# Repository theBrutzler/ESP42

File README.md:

# ESP42
ESP42 -> ESP01

it has 4MB Flash and 2MB of Ram

I created a board, that could fit an ESP32 on a ESP01 standard pinout.

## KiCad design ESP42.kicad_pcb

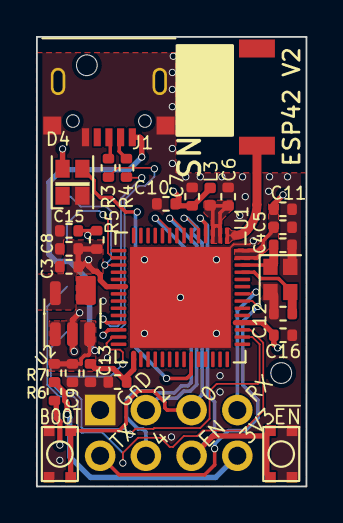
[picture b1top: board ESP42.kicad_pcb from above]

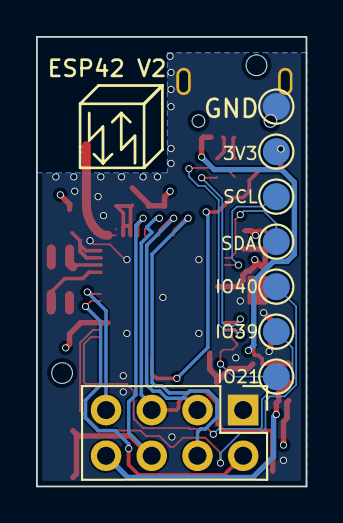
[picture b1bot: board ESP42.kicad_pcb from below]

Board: 4 copper layers, 15.0 x 25.0 mm, 37 parts (9 on the bottom side), 25 nets.

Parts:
3V3: TestPoint; TestPoint_Pad_D1.5mm
AE1: Antenna_Shield; RFANT5220110A2T
C3, C9: 10µ; R_0402_1005Metric
C4, C12: 15p; R_0402_1005Metric
C5, C6, C7, C8, C14, C16: 100n; R_0402_1005Metric
C10, C11, C13, C15: 1µ; R_0402_1005Metric
D4: WS2812B_Geaendertes_Symbol; LED_Cree-PLCC4_2x2mm_CCW
GND: TestPoint; TestPoint_Pad_D1.5mm
IO21, IO39, IO40: TestPoint; TestPoint_Pad_D1.5mm
J1: USB_B_Micro; 10118194
J2: Conn_02x04_Odd_Even; PinHeader_2x04_P2.54mm_Vertical
L3: 2n2; L_0402_1005Metric
R3, R4: 22; R_0402_1005Metric
R5: 5K1; R_0402_1005Metric
R6, R7: 0; R_0402_1005Metric
SCL: TestPoint; TestPoint_Pad_D1.5mm
SDA: TestPoint; TestPoint_Pad_D1.5mm
SM3: SYM_Arrow45_Tiny; Symbol_kurzschlussblog
SW1, SW2: SW_Push; microswitch
U1: ESP32-S3; QFN-56-1EP_7x7mm_P0.4mm_EP5.6x5.6mm
U2: LN1134A332MR; TSOT-23-5
Y1: 40MHz; Crystal_SMD_2016-4Pin_2.0x1.6mm

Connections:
+3V3: 3V3.1, C3.1, C5.2, C7.2, C8.2, C10.2, C11.2, C16.2, D4.4 (VDD), L3.1, R5.1, R6.2, U1.20 (VDD3P3_RTC), U1.46 (VDD3P3_CPU), U1.55 (VDDA), U1.56 (VDDA), U2.5 (VOUT)
/D+: R3.1, U1.26 (GPIO20/USB_D+/ADC2_CH9)
/D-: R4.1, U1.25 (GPIO19/USB_D-/ADC2_CH8)
/EN: C15.1, J2.6, R5.2, SW1.2, U1.4 (CHIP_PU/RESET)
/IO0: J2.5, SW2.2, U1.5 (GPIO0/BOOT)
/IO2: J2.3, U1.7 (GPIO2/ADC1_CH1)
/IO4: J2.4, U1.9 (GPIO4/ADC1_CH3)
/IO47: D4.3 (DIN), U1.37 (SPICLK_P/GPIO47)
/RX: J2.7, U1.50 (U0RXD/PROG/GPIO44)
/SCL: SCL.1, U1.17 (GPIO12/ADC2_CH1)
/SDA: SDA.1, U1.16 (GPIO11/ADC2_CH0)
/TX: J2.2, U1.49 (U0TXD/PROG/GPIO43)
/VIN: C9.1, J1.1 (VBUS), R7.1, U2.1 (VIN), U2.3 (EN)
GND: C3.2, C4.2, C5.1, C6.1, C7.1, C8.1, C9.2, C10.1, C11.1, C12.2, C13.1, C14.1, C15.2, C16.1, D4.2 (VSS), GND.1, J1.5 (GND), J1.6 (Shield), J2.1, SW1.1, SW2.1, U1.57 (GND), U2.2 (GND), Y1.2, Y1.4
unnamed: AE1.1 (A), U1.1 (LNA_IN/RF)
unnamed: J1.3 (D+), R3.2
unnamed: J1.2 (D-), R4.2
unnamed: J2.8, R6.1, R7.2
unnamed: IO21.1, U1.27 (GPIO21)
unnamed: IO39.1, U1.44 (MTCK/JTAG/GPIO39)
unnamed: IO40.1, U1.45 (MTDO/JTAG/GPIO40)
unnamed: C13.2, C14.2, U1.29 (VDD_SPI)
unnamed: C12.1, U1.53 (XTAL_N), Y1.3
unnamed: C4.1, U1.54 (XTAL_P), Y1.1
VDD3P3: C6.2, L3.2, U1.2 (VDD3P3), U1.3 (VDD3P3)

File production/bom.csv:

Designator,Footprint,Quantity,Value,LCSC Part #
AE1,RFANT5220110A2T,1,Antenna_Shield,C201761
"C10, C11, C13, C15",0402,4,1µ,C14445
"C12, C4",0402,2,15p,C86285
"C14, C16, C5, C6, C7, C8",0402,6,100n,C1525
"C3, C9",0402,2,10µ,C315248
D4,LED_Cree-PLCC4_2x2mm_CCW,1,WS2812B_Geaendertes_Symbol,C965556
IO21,TestPoint_Pad_D1.5mm,1,TestPoint,
J1,10118194,1,USB_B_Micro,C2926988
L3,0402,1,2n2,C2941466
"R3, R4",0402,2,22,C25152
R5,0402,1,5K1,C25905
R6,0402,1,0,C21376
SM3,Symbol_kurzschlussblog,1,SYM_Arrow45_Tiny,
"SW1, SW2",microswitch,2,SW_Push,C100056
U1,QFN-56-1EP_7x7mm_P0.4mm_EP5.6x5.6mm,1,ESP32-S3,C3013940
U2,TSOT-23-5,1,LN1134A332MR,C141419
Y1,Crystal_SMD_2016-4Pin_2.0x1.6mm,1,40MHz,C424431

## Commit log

2023-08-29 initial upload
2023-08-29 add readme
